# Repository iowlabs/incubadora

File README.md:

# incubadora

Hola estamos probando el flujo de git

This project consists of a low-cost incubator for biotechnology instrumentation. Its design is easy to integrate and adaptable to different scenarios. It is ideal for remote laboratories, field deployments, school laboratories, and educational kits.

For this project, a PCB was designed that implements the electronics to control the operation of an incubator. It includes a temperature control and a *shaker* for sample agitation.

The PCB is based on a ESP32 so It can implement remote control and monitoring via Wi-Fi or BLE. It also has access to a USB communication interface for parameter configuration, curve generation, and data acquisition. It also features a simple interface that uses an LCD display and a rotary encoder as an alternative control method.

## Features.

### General features:

- Temperature Control
- Shaker RPM Control
- Simple User Interface
- WiFi Remote Control Capability
- Temperature profile programming
- easy assembly

### Hardware Features

- ESP32 Microcontroller
- PID Temperature Control Loop
	- Heater: Peltier-controlled by a H-bridge (2 separated heater channels)
	- Temperature Sensor: SHT31 ambient temperature and humidity sensor via I²C
	- Fan Assembly
- Shaker Control:
	- Nema 17 Motor
	- DRV8825 Polulu Controller
- Local User Interface
	- Rotary Encoder
	- LCD Display
	- SD Card
- WiFi Remote Control
	- MQTT Commands
- INA219 Current Sensor for Measuring Input Power Consumption

---
# Documentación

- Github repo
- Web

## Licencias

|     |   Licence |
|---- | --------- |
|Hardware | --------- |
|Firmware and Software | --------- |
|Documentation and files | --------- |

---

# Diseño e implementación

---

## PCB
### Schematic

### pcb BOM

---

## Case 3D and structure

---

## List of components

### Assembly steps

---

## Firmware

### Used libraries

### Structure of the code

### Available Features.

---

# Application examples

## Using a portable cooler as incubator.

## Using a large incubator.

## Code to acquire and plot data in real time.

## Controlling via MQTT.

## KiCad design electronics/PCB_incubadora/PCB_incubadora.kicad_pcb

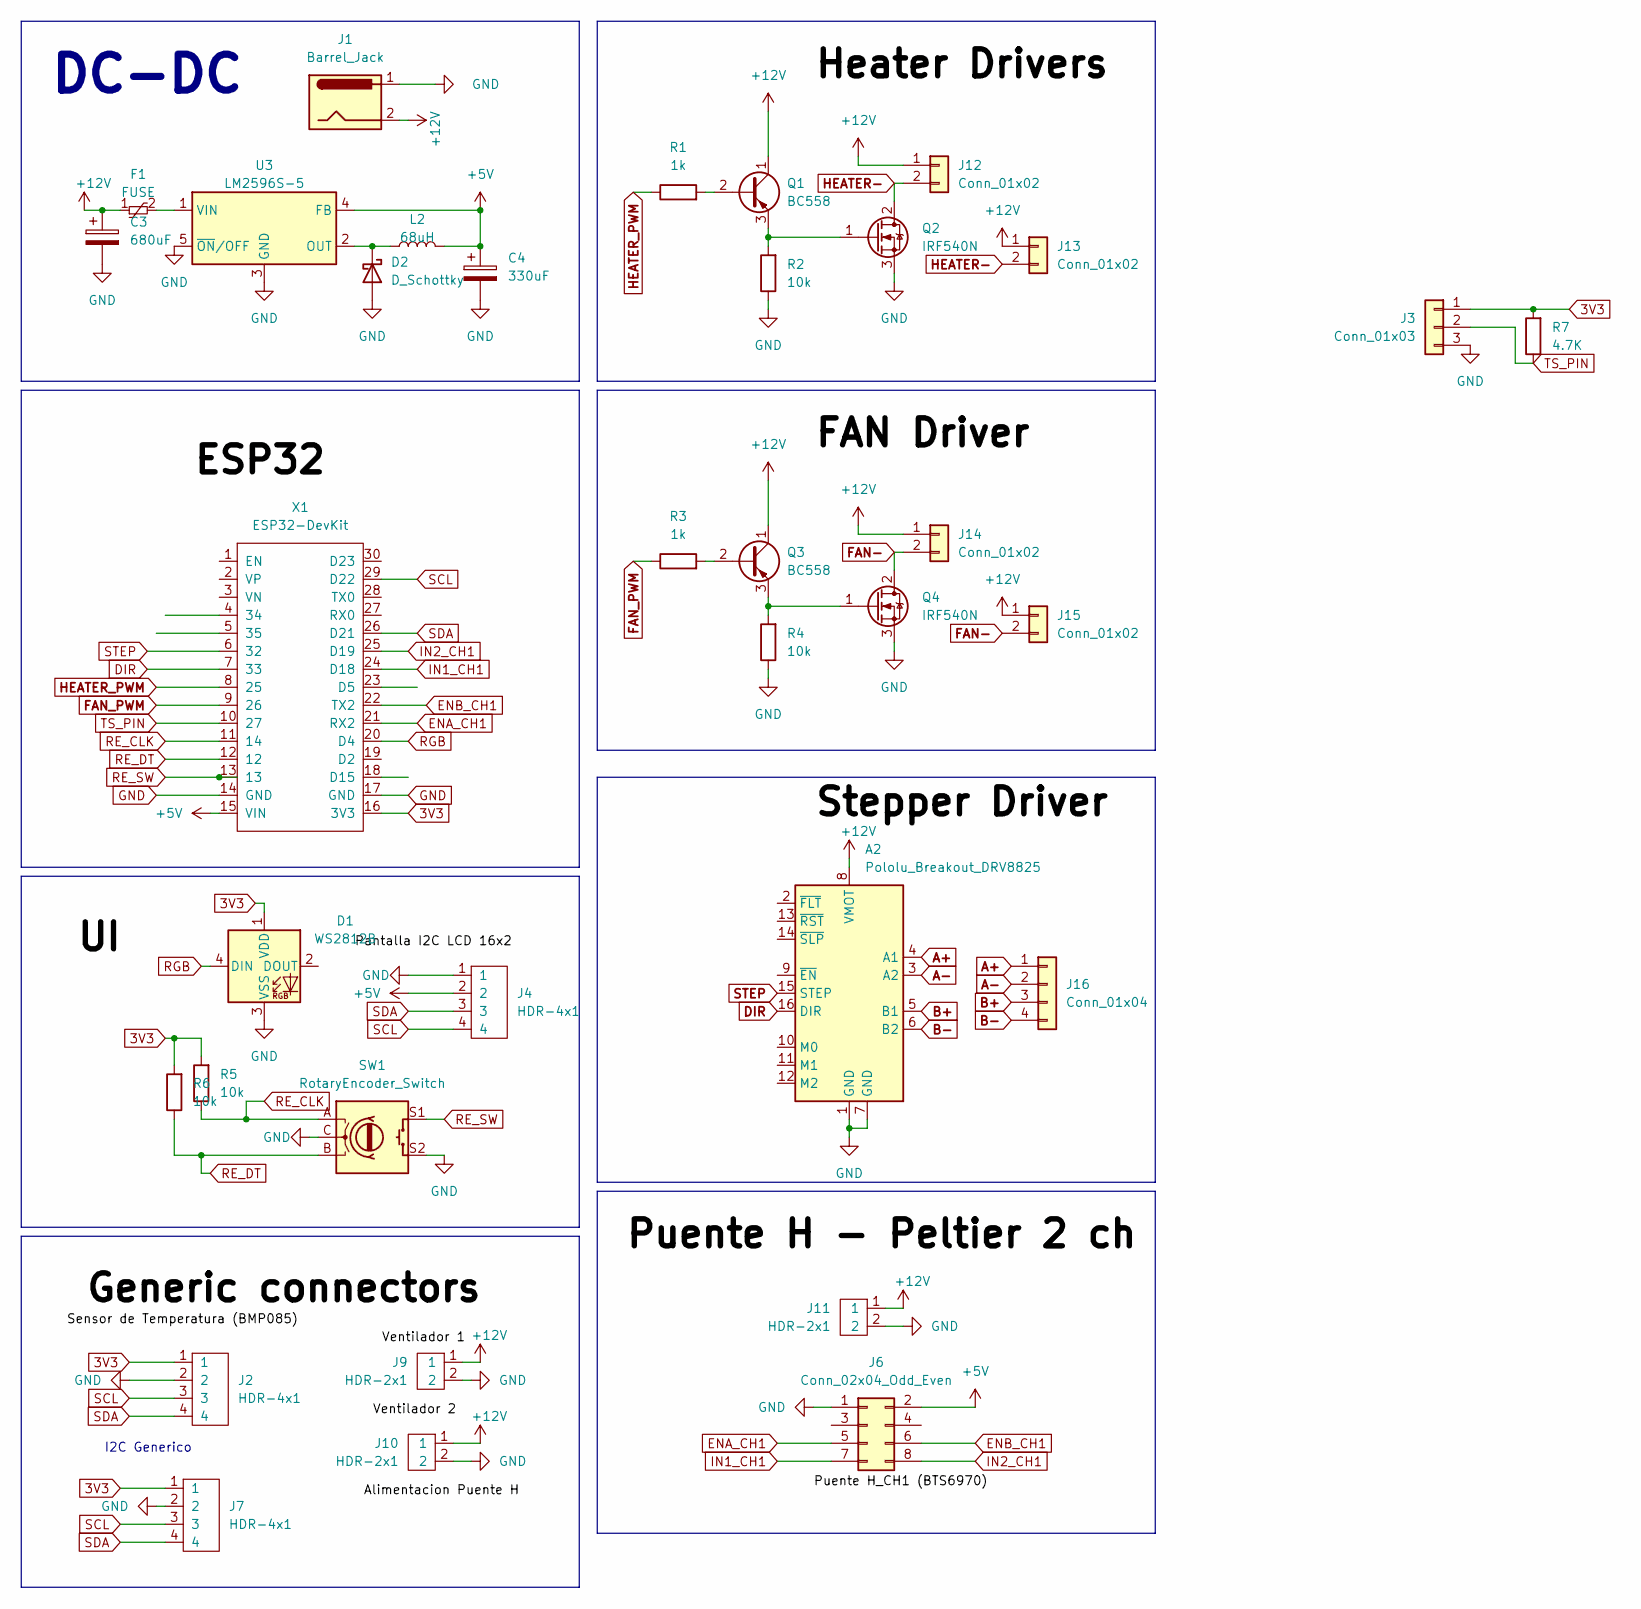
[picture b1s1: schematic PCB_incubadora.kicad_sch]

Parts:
A2: Pololu_Breakout_DRV8825; Pololu_Breakout-16_15.2x20.3mm
C3: 680uF; CP_Elec_10x10
C4: 330uF; CP_Elec_10x10
D1: WS2812B; LED_WS2812B_PLCC4_5.0x5.0mm_P3.2mm
D2: D_Schottky; D_SMB_Handsoldering
F1: FUSE; Fuse_1206_3216Metric
J1: Barrel_Jack; BarrelJack_Horizontal
J2, J7: HDR-4x1; JST_XH_B4B-XH-A_1x04_P2.50mm_Vertical
J3: Conn_01x03
J4: HDR-4x1; OLED 0'96 SPI module
J6: Conn_02x04_Odd_Even; PinHeader_2x04_P2.54mm_Vertical
J9, J10, J11: HDR-2x1; TerminalBlock_4Ucon_1x02_P3.50mm_Horizontal
J12, J13, J14, J15: Conn_01x02; TerminalBlock_4Ucon_1x02_P3.50mm_Horizontal
J16: Conn_01x04; TerminalBlock_4Ucon_1x04_P3.50mm_Horizontal
L2: 68uH; L_12x12mm_H6mm
Q1, Q3: BC558; TO-92_Inline
Q2, Q4: IRF540N; TO-220-3_Vertical
R1, R3: 1k; R_0603_1608Metric
R2, R4, R5, R6: 10k; R_0603_1608Metric
R7: 4.7K; R_0603_1608Metric
SW1: RotaryEncoder_Switch; RotaryEncoder_Alps_EC11E-Switch_Vertical_H20mm
U3: LM2596S-5; TO-263-5_TabPin3
X1: ESP32-DevKit; ESP32_devkit

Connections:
3V3: D1.1 (VDD), J2.1, J3.1, J7.1, R5.2, R6.2, R7.2, X1.16 (3V3)
+5V: C4.1, J4.2, J6.2, L2.2, U3.4 (FB), X1.15 (VIN)
+12V: A2.8 (VMOT), C3.1, F1.1, J1.2, J9.1, J10.1, J11.1, J12.1, J13.1, J14.1, J15.1, Q1.1 (C), Q3.1 (C)
A+: A2.4 (A1), J16.1
A-: A2.3 (A2), J16.2
B+: A2.5 (B1), J16.3
B-: A2.6 (B2), J16.4
DIR: A2.16 (DIR), X1.7 (33)
ENA_CH1: J6.5, X1.21 (RX2)
ENB_CH1: J6.6, X1.22 (TX2)
FAN-: J14.2, J15.2, Q4.2 (D)
FAN_PWM: R3.1, X1.9 (26)
GND: A2.1 (GND), A2.7 (GND), C3.2, C4.2, D1.3 (VSS), D2.2 (A), J1.1, J2.2, J3.3, J4.1, J6.1, J7.2, J9.2, J10.2, J11.2, Q2.3 (S), Q4.3 (S), R2.1, R4.1, SW1.C, SW1.S2, U3.3 (GND), U3.5 (~ON/OFF), X1.14 (GND), X1.17 (GND)
HEATER-: J12.2, J13.2, Q2.2 (D)
HEATER_PWM: R1.1, X1.8 (25)
IN1_CH1: J6.7, X1.24 (D18)
IN2_CH1: J6.8, X1.25 (D19)
unnamed: D2.1 (K), L2.1, U3.2 (OUT)
unnamed: J3.2, R7.1, X1.10 (27)
unnamed: Q1.2 (B), R1.2
unnamed: Q1.3 (E), Q2.1 (G), R2.2
unnamed: Q3.2 (B), R3.2
unnamed: Q3.3 (E), Q4.1 (G), R4.2
unnamed: F1.2, U3.1 (VIN)
RE_CLK: R5.1, SW1.A, X1.11 (14)
RE_DT: R6.1, SW1.B, X1.12
RE_SW: SW1.S1, X1.13
RGB: D1.4 (DIN), X1.20 (D4)
SCL: J2.3, J4.4, J7.3, X1.29 (D22)
SDA: J2.4, J4.3, J7.4, X1.26 (D21)
STEP: A2.15 (STEP), X1.6 (32)

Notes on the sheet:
I2C Generico
DC-DC

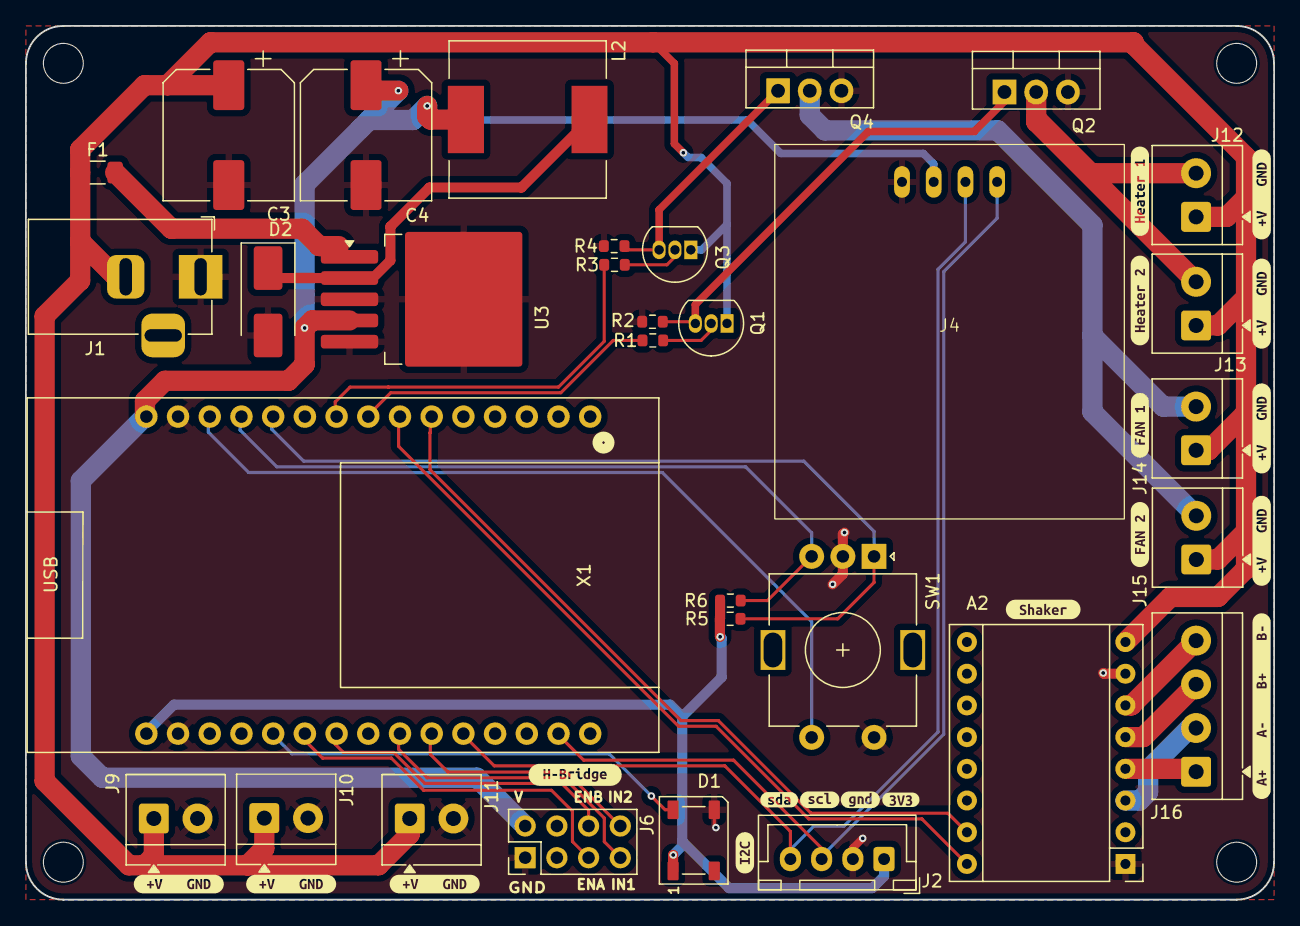
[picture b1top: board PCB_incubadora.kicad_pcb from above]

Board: 2 copper layers, 100.0 x 70.0 mm, 51 parts (0 on the bottom side), 30 nets.

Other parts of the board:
kibuzzard-6A5B10A0: G***; kibuzzard-6A5B10A0
kibuzzard-6A5B10F5, kibuzzard-6A5B10F5#2, kibuzzard-6A5B10F5#3, kibuzzard-6A5B10F5#4, kibuzzard-6A5B10F5#5, kibuzzard-6A5B10F5#6, kibuzzard-6A5B10F5#7: G***; kibuzzard-6A5B10F5
kibuzzard-6A5B11C6: G***; kibuzzard-6A5B11C6
kibuzzard-6A5B13D0: G***; kibuzzard-6A5B13D0
kibuzzard-6A5B13E5: G***; kibuzzard-6A5B13E5
kibuzzard-6A5B13F6: G***; kibuzzard-6A5B13F6
kibuzzard-6A5B162D: G***; kibuzzard-6A5B162D
kibuzzard-6A5B1115: G***; kibuzzard-6A5B1115
kibuzzard-6A5B1189: G***; kibuzzard-6A5B1189
kibuzzard-6A5B1258: G***; kibuzzard-6A5B1258
kibuzzard-6A5B1282: G***; kibuzzard-6A5B1282
kibuzzard-6A5B1312: G***; kibuzzard-6A5B1312
kibuzzard-6A5B1426: G***; kibuzzard-6A5B1426

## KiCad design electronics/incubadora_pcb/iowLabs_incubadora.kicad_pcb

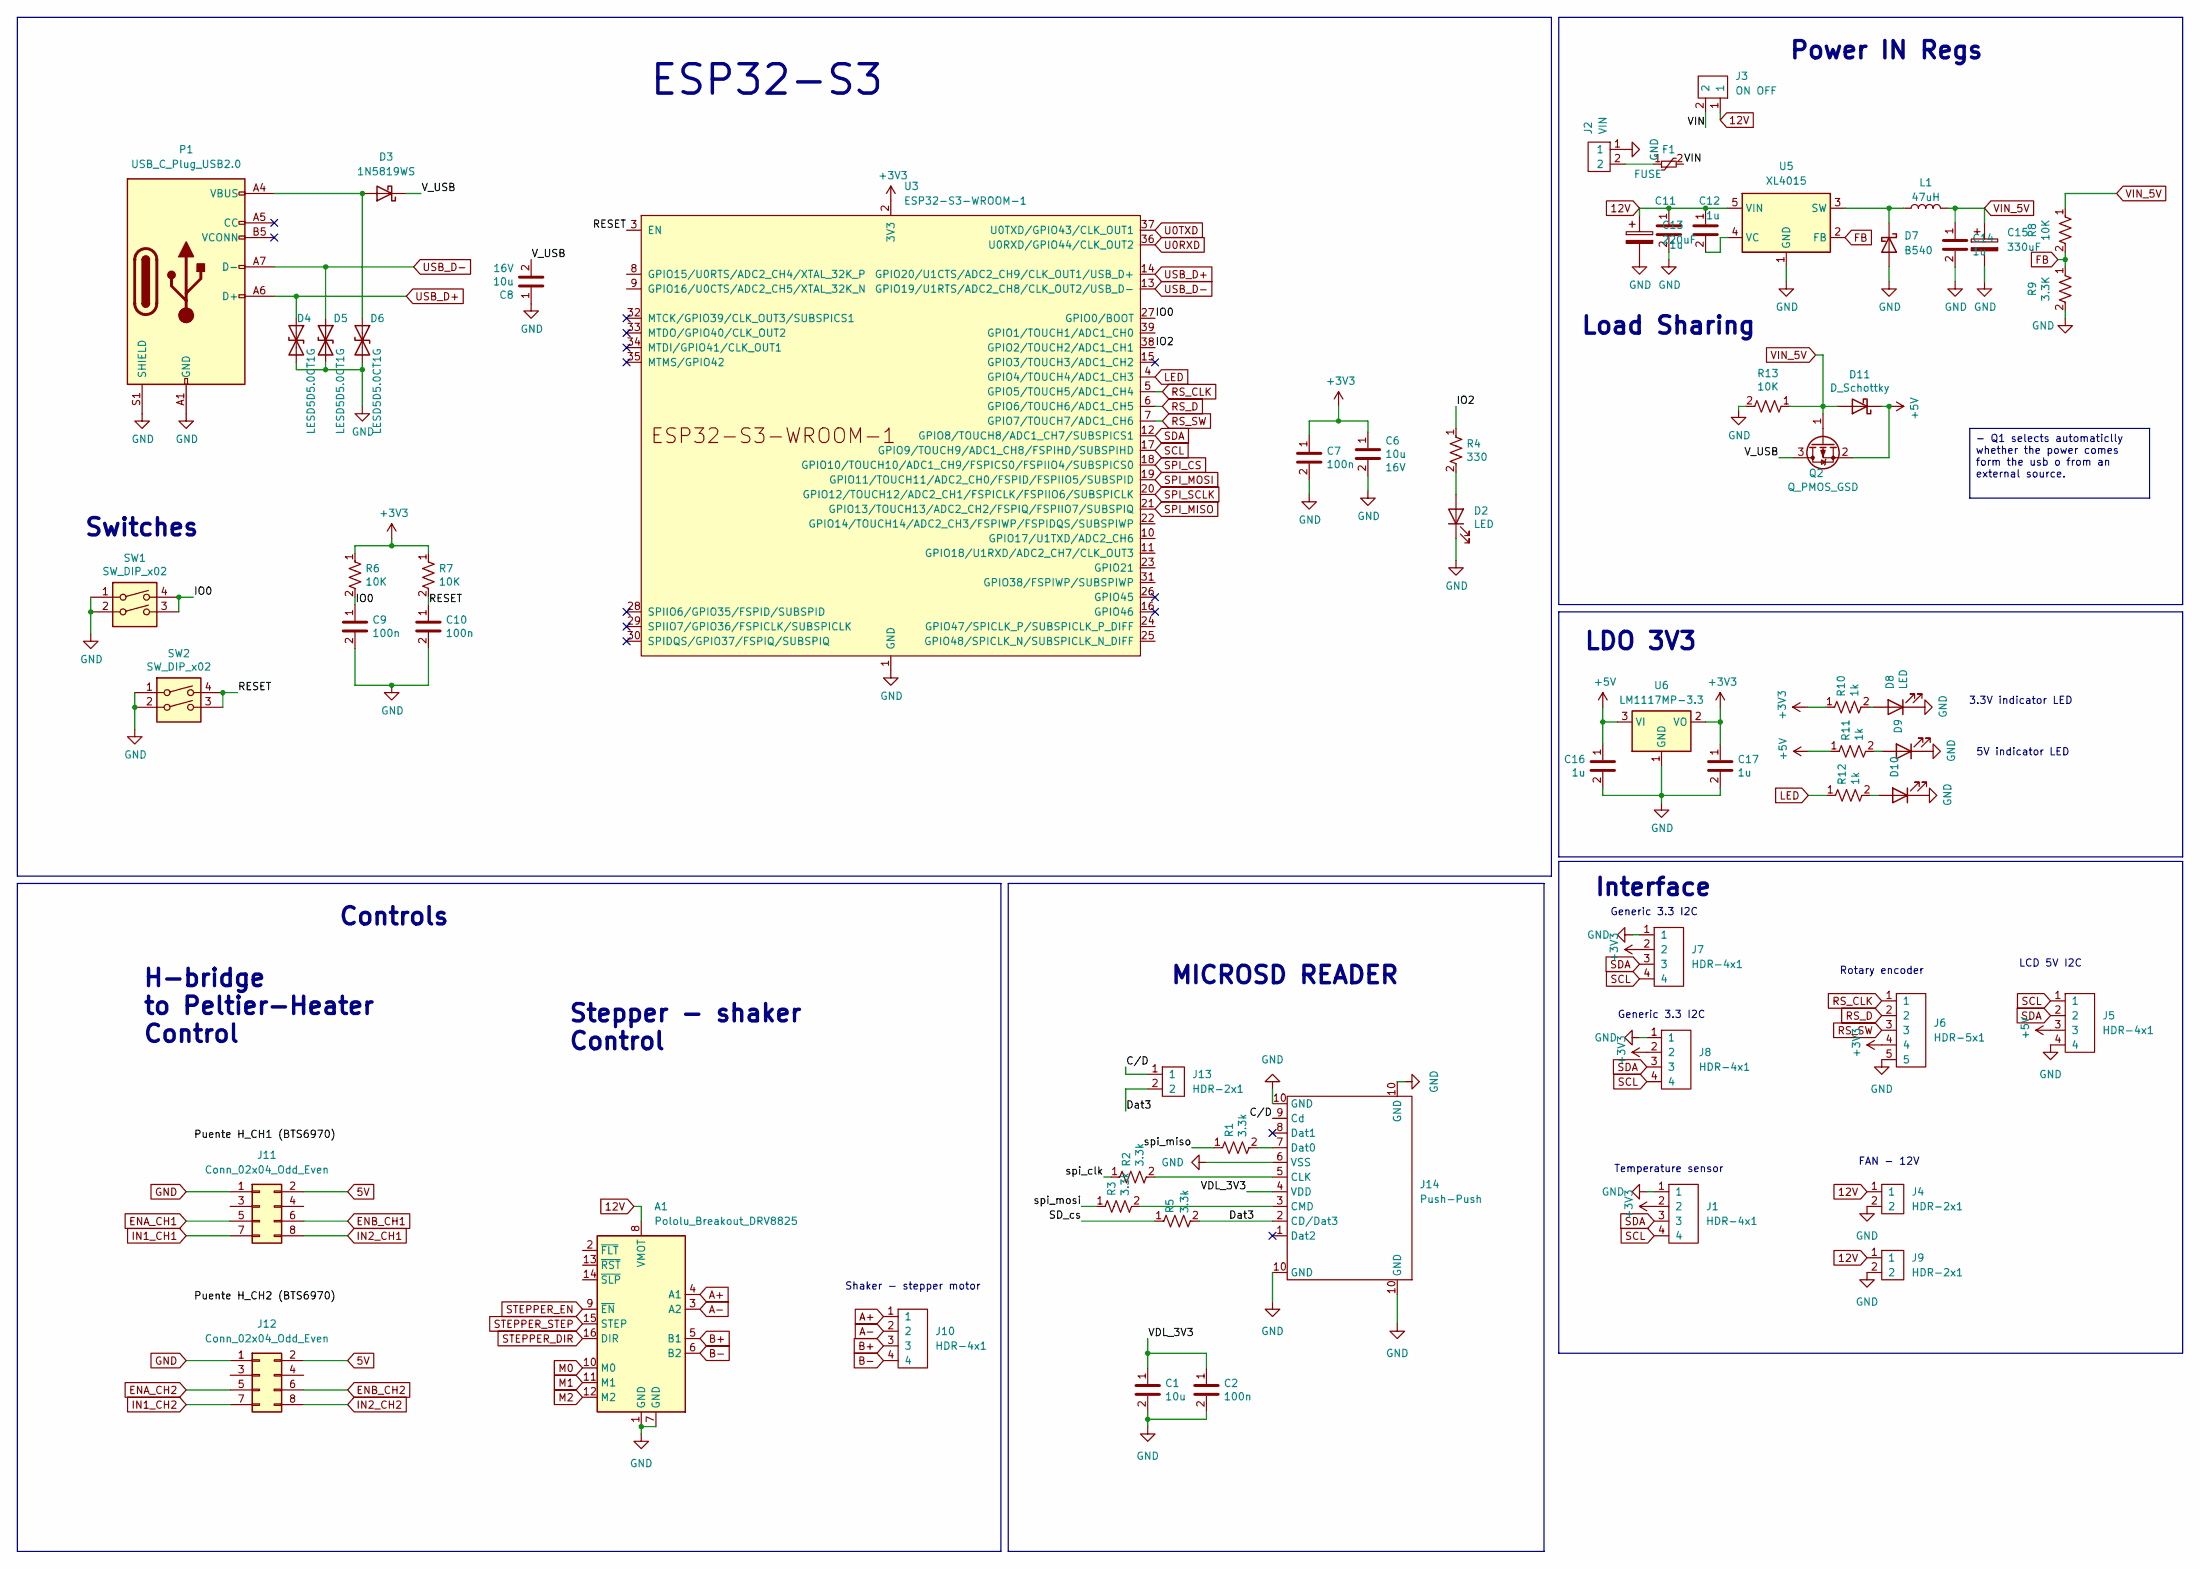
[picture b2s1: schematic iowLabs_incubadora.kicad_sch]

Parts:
A1: Pololu_Breakout_DRV8825; Pololu_Breakout-16_15.2x20.3mm
C1, C6, C8: 10u; C_0805_2012Metric; Voltage rated 16V
C2, C7, C9, C10: 100n; C_0603_1608Metric; Voltage rated 16V
C11, C12, C14, C16, C17: 1u; C_0805_2012Metric; Voltage rated 16V
C13: 220uF; CP_Elec_8x10.5; Voltage 50V
C15: 330uF; CP_Elec_8x10.5; Voltage 25V
D2, D8, D9, D10: LED; LED_0603_1608Metric
D3: 1N5819WS; D_SOD-323
D4, D5, D6: LESD5D5.0CT1G; D_SOD-523
D7: B540; D_SMB_Handsoldering
D11: D_Schottky; D_SMA
F1: FUSE; Fuse_1206_3216Metric
J1, J5, J7, J8, J10: HDR-4x1; JST_XH_B4B-XH-A_1x04_P2.50mm_Vertical
J2: VIN; Tb-2x1-5p-TH-V
J3: ON OFF; PinHeader_1x02_P2.54mm_Vertical
J4, J9: HDR-2x1
J6: HDR-5x1; JST_XH_B5B-XH-A_1x05_P2.50mm_Vertical
J11, J12: Conn_02x04_Odd_Even; PinHeader_2x04_P2.54mm_Vertical
J13: HDR-2x1; PinHeader_1x02_P2.54mm_Vertical
J14: microSD_push_push
L1: 47uH; L_12x12mm_H8mm
P1: USB_C_Plug_USB2.0; USB_C_Receptacle_GCT_USB4105-xx-A_16P_TopMnt_Horizontal
Q2: Q_PMOS_GSD; SOT-23
R1, R2, R3, R5: 3.3k; R_0603_1608Metric
R4: 330; R_0603_1608Metric
R6, R7, R8, R13: 10K; R_0603_1608Metric
R9: 3.3K; R_0603_1608Metric
R10, R11, R12: 1k; R_0603_1608Metric
SW1, SW2: SW_DIP_x02; SMD_SWITCH
U3: ESP32-S3-WROOM-1
U5: XL4015; TO-263-5_TabPin3
U6: LM1117MP-3.3; SOT-223-3_TabPin2

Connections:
5V: J11.2, J12.2
12V: A1.8 (VMOT), C11.1, C12.1, C13.1, J3.1, J4.1, J9.1, U5.5 (VIN)
+3V3: C6.1, C7.1, C17.1, J1.2, J6.4, J7.2, J8.2, R6.1, R7.1, R10.1, U3.2 (3V3), U6.2 (VO)
+5V: C16.1, D11.1 (K), J5.3, Q2.2 (S), R11.1, U6.3 (VI)
/C/D: J13.1, J14.9 (Cd)
/Dat3: J13.2, J14.2 (CD/Dat3), R5.2
/IO0: C9.1, R6.2, SW1.3, SW1.4, U3.27 (GPIO0/BOOT)
/IO2: R4.1, U3.38 (GPIO2/TOUCH2/ADC1_CH1)
/RESET: C10.1, R7.2, SW2.3, SW2.4, U3.3 (EN)
/SD_cs: R5.1
/VDL_3V3: C1.1, C2.1, J14.4 (VDD)
/VIN: F1.2, J3.2
/V_USB: C8.2, D3.1 (K), Q2.3 (D)
/spi_clk: R2.1
/spi_miso: R1.1
/spi_mosi: R3.1
A+: A1.4 (A1), J10.1
A-: A1.3 (A2), J10.2
B+: A1.5 (B1), J10.3
B-: A1.6 (B2), J10.4
ENA_CH1: J11.5
ENA_CH2: J12.5
ENB_CH1: J11.6
ENB_CH2: J12.6
FB: R8.2, R9.1, U5.2 (FB)
GND: A1.1 (GND), A1.7 (GND), C1.2, C2.2, C6.2, C7.2, C8.1, C9.2, C10.2, C11.2, C13.2, C14.2, C15.2, C16.2, C17.2, D2.1 (K), D4.2 (A2), D5.2 (A2), D6.2 (A2), D7.2 (A), D8.1 (K), D9.1 (K), D10.1 (K), J1.1, J2.1, J4.2, J5.4, J6.5, J7.1, J8.1, J9.2, J11.1, J12.1, J14.6 (VSS), J14.10 (GND), P1.A1 (GND), P1.A12 (GND), P1.B1 (GND), P1.B12 (GND), P1.S1 (SHIELD), R9.2, R13.2, SW1.1, SW1.2, SW2.1, SW2.2, U3.1 (GND), U3.40 (GND), U3.41 (GND), U5.1 (GND), U6.1 (GND)
IN1_CH1: J11.7
IN1_CH2: J12.7
IN2_CH1: J11.8
IN2_CH2: J12.8
LED: R12.1, U3.4 (GPIO4/TOUCH4/ADC1_CH3)
M0: A1.10 (M0)
M1: A1.11 (M1)
M2: A1.12 (M2)
unnamed: D2.2 (A), R4.2
unnamed: D3.2 (A), D6.1 (A1), P1.A4 (VBUS), P1.A9 (VBUS), P1.B4 (VBUS), P1.B9 (VBUS)
unnamed: D7.1 (K), L1.1, U5.3 (SW)
unnamed: D8.2 (A), R10.2
unnamed: D9.2 (A), R11.2
unnamed: D10.2 (A), R12.2
unnamed: F1.1, J2.2
unnamed: J14.5 (CLK), R2.2
unnamed: J14.3 (CMD), R3.2
unnamed: J14.7 (Dat0), R1.2
unnamed: C12.2, U5.4 (VC)
RS_CLK: J6.1, U3.5 (GPIO5/TOUCH5/ADC1_CH4)
RS_D: J6.2, U3.6 (GPIO6/TOUCH6/ADC1_CH5)
RS_SW: J6.3, U3.7 (GPIO7/TOUCH7/ADC1_CH6)
SCL: J1.4, J5.1, J7.4, J8.4, U3.17 (GPIO9/TOUCH9/ADC1_CH8/FSPIHD/SUBSPIHD)
SDA: J1.3, J5.2, J7.3, J8.3, U3.12 (GPIO8/TOUCH8/ADC1_CH7/SUBSPICS1)
SPI_CS: U3.18 (GPIO10/TOUCH10/ADC1_CH9/FSPICS0/FSPIIO4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)
SPI_MISO: U3.21 (GPIO13/TOUCH13/ADC2_CH2/FSPIQ/FSPIIO7/S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)
SPI_MOSI: U3.19 (GPIO11/TOUCH11/ADC2_CH0/FSPID/FSPIIO5/S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)
SPI_SCLK: U3.20 (GPIO12/TOUCH12/ADC2_CH1/FSPICLK/FSPIIO6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)
STEPPER_DIR: A1.16 (DIR)
STEPPER_EN: A1.9 (~EN)
STEPPER_STEP: A1.15 (STEP)
U0RXD: U3.36 (U0RXD/GPIO44/CLK_OUT2)
U0TXD: U3.37 (U0TXD/GPIO43/CLK_OUT1)
USB_D+: D4.1 (A1), P1.A6 (D+), U3.14 (GPIO20/U1CTS/ADC2_CH9/CLK_OUT1/USB_D+)
USB_D-: D5.1 (A1), P1.A7 (D-), U3.13 (GPIO19/U1RTS/ADC2_CH8/CLK_OUT2/USB_D-)
VIN_5V: C14.1, C15.1, D11.2 (A), L1.2, Q2.1 (G), R8.1, R13.1

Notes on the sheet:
LCD 5V I2C
3.3V indicator LED
H-bridge to Peltier-Heater Control
MICROSD READER
Power IN Regs
Load Sharing
5V indicator LED
Interface
FAN - 12V
Shaker - stepper motor
Controls
Generic 3.3 I2C
Stepper - shaker Control
Switches
ESP32-S3
Rotary encoder
LDO 3V3
Temperature sensor
- Q1 selects automaticlly whether the power comes form the usb o from an external source.

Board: 2 copper layers, 59 parts (0 on the bottom side), 38 nets, no tracks yet.

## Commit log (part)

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2024-11-23 testing heater control
2024-11-24 basic configuration of the complete sistem. working
2024-11-30 adding LCD showint temp
2024-11-30 minor changes on main.cpp
2025-06-25 adding sch
2025-07-21 changing temp sensor
2025-07-23 shanging sensor
2026-03-30 Major firmware/web control update: API UI, motor fixes, and test setup
